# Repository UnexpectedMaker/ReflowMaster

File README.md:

# ReflowMaster

ReflowMaster is my original open source toaster oven reflow controller that I used to sell on tindie:
https://www.tindie.com/products/13378/

### This project is not compatible with ReflowMasterPro

It's custom hardware and custom code but all open source so if you want the challenge of making one yourself or you want to hack the code, go for it!

I have a live stream build of the board here if you want to see what's involved
https://www.youtube.com/watch?v=OGQ-GZZ90oE

# ReflowMaster Design Files

Included in this repository:
- EagleCAD schematics and Board layout files (Eagle 9.1) 
- Exported Gerber files (Gerber 274X)
- STL files for the 3D printed case
- Adrduino code

# Open Source License
The hardware design files are released as open source under the CERN license. Please review the license before using these files in your own projects to understand your obligations.

# STL files for 3D printing
I have included the STL files for the case and also the exhaust fan adapter I made for my specific toaster oven. 

**NOTE:** Do not print the exhaust fan in PLA, please use PET-G or ABS as PLA warps/melts at a low temp. Also DO NOT connect the 3D printed exhaust fan directly to the metal of teh oven, it will melt and ruin your oven. You will need to add some heat resistant insulator between the metal and the 3D print. 

# Which TFT?
The TFT I am using is a 2.4" SPI TFT using the ILI9341 Driver available via...

AliExpress
https://s.click.aliexpress.com/e/_DevvrLr

Ebay
https://rover.ebay.com/rover/1/705-53470-19255-0/1?icep_id=114&ipn=icep&toolid=20004&campid=5338252684&mpre=https%3A%2F%2Fwww.ebay.com.au%2Fitm%2F2-4-240x320-SPI-TFT-LCD-Serial-240-320-ILI9341-PCB-Adapter-SD-Card-M52%2F291549777432%3FssPageName%3DSTRK%253AMEBIDX%253AIT%26_trksid%3Dp2057872.m2749.l2649

# SAMD21 Bootloader
If you build your own Reflow Master, you will need to use a SAMD21G18 that already has an Arduino bootloader on it *before* it is put on the board. If you need to add a bootloader, you'll need an ATMEL ICE and an adapter for the chip. The cheapest adapter you can get is my SAMD21G Mangler available here...
https://www.tindie.com/products/13379/

# Updating firmware & Adding profiles - for Version 2.0.0
You can flash your Reflow Master with the Arduino IDE using the code provided above.

If you wish to add or change any of the reflow profiles, you need to do so in the code and re-flash the changes to your Reflow Master.

The Reflow Master board works like an "Adafruit Feather M0" - so you'll need to have the Adafruit Cortex m0 hardware profiles installed as well as the regular Cortex m0 Arduino profiles.

You can use the instructions here to install everything you need to get up and running in the Arduino IDE:
https://learn.adafruit.com/adafruit-feather-m0-basic-proto/setup

You will also need the following libraries from Library Manager
- One Button
- Adafruit_GFX
- Adafruit_ILI9341

Once you have everything you need, you can download the code from this repo and put it into the Arduino folder where your sketches are stored, load the sketch, select Adafruit Feather M0 from the boards list, plug in your RM and turn it on, and select the correct port from the ports list and flash.
   
The easiest way to put a new profile into the code is to change one of the existing profiles, by altering the values in it's class initialiser. Information of what each value is is available in the ReflowMasterProfile.h file:
https://github.com/UnexpectedMaker/ReflowMaster/blob/master/Code/Reflow_Master_v2/ReflowMasterProfile.h
   
Enjoy!

# Support Unexpected Maker

I love designing, making and releasing my projects as open source. I do it because I believe it’s important to share knowledge and give back to the community, like many have done before me. It helps us all learn and grow.

That said, a lot of time, effort and finances have gone into designing and releasing these files, so please consider supporting me by buying some of my products:

https://unexpectedmaker.com/shop

https://www.tindie.com/stores/seonr/

Or by becoming a Patron:

https://www.patreon.com/unexpectedmaker

# Join my discord server
https://discord.com/invite/xAHpApP

# Unexpected Maker
https://unexpectedmaker.com

http://youtube.com/unexpectedmaker

http://twitter.com/unexpectedmaker

https://www.facebook.com/unexpectedmaker/

https://www.instagram.com/unexpectedmaker/

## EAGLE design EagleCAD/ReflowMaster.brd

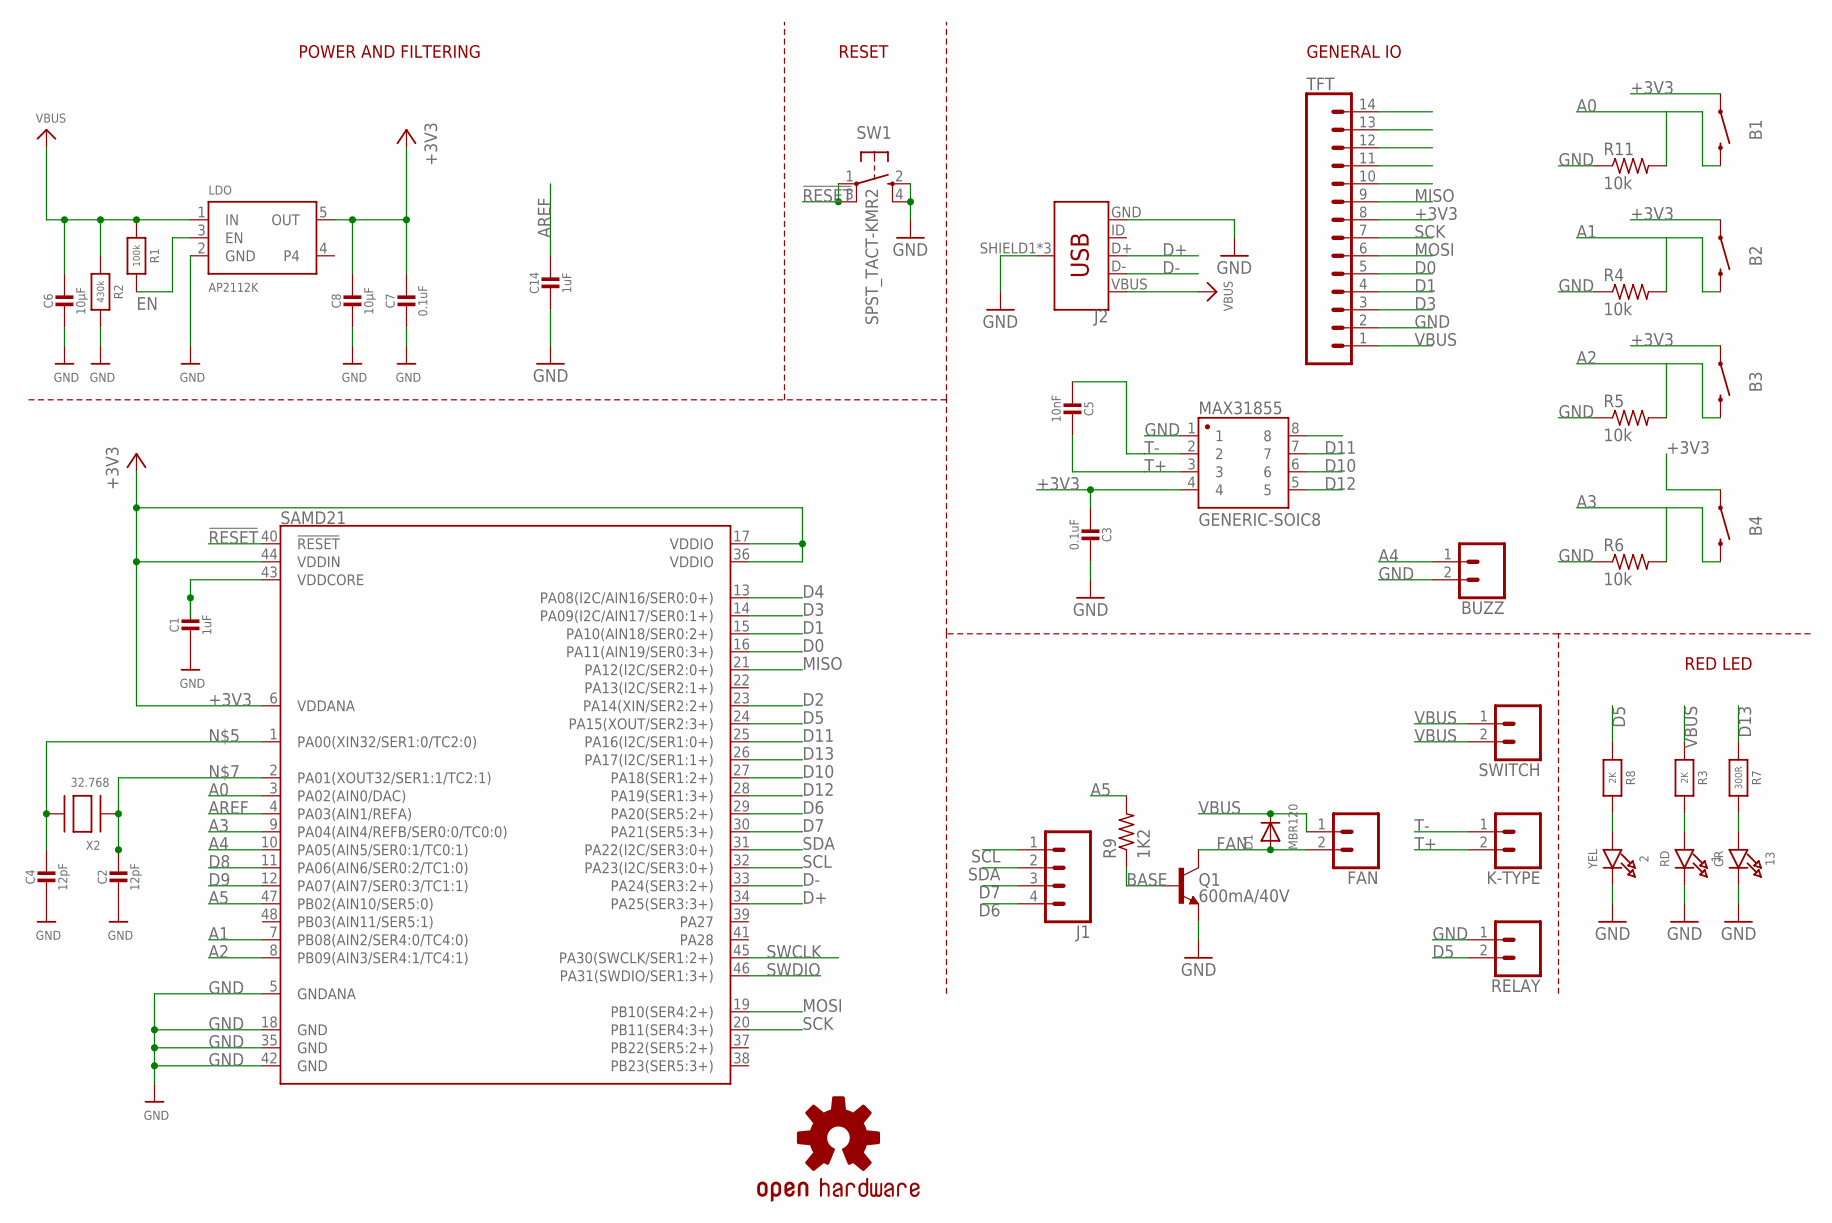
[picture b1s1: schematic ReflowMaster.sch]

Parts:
1: RD; CHIPLED_0805_NOOUTLINE
2: YEL; CHIPLED_0805_NOOUTLINE
13: GR; CHIPLED_0805_NOOUTLINE
B1, B2, B3, B4: MOMENTARY-SWITCH-SPST-PTH-RIGHT-ANGLE-KIT; TACTILE_SWITCH_PTH_RIGHT_ANGLE_KIT
BUZZ: CONN_02; 1X02
C1, C14: 1uF; 0805-NO
C2, C4: 12pF; 0805-NO
C3, C7: 0.1uF; 0805-NO
C5: 10nF; 0805-NO
C6, C8: 10µF; 0805-NO
D1: MBR120; SOD-123
FAN: CONN_02; 1X02
J1: CONN_041X04_NO_SILK; 1X04_NO_SILK
J2: USB_MICRO-B_FEMALE-SMT; USB-B-MICRO-SMD
K-TYPE: CONN_02; 1X02
LDO: AP2112K; SOT23-5
LOGO1: OSHW-LOGOS; OSHW-LOGO-S
MAX31855: GENERIC-SOIC8; SO08-UNIVERSAL
Q1: 600mA/40V; SOT23-3
R1: 100k; 0805-NO
R2: 430k; 0805-NO
R3, R8: 2K; 0805-NO
R4, R5, R6, R11: 10k; R0805
R7: 300R; 0805-NO
R9: 1K2; R0805
RELAY: CONN_02; 1X02
SAMD21: ATSAMD21G-A; TQFP-48
SW1: SPST_TACT-KMR2; KMR2
SWITCH: CONN_02; 1X02
TFT: CONN_14NO_SILK; 1X14_NO_SILK
X2: 32.768; XTAL3215

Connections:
!RESET: SAMD21.40 (!RESET!), SW1.1, SW1.3 (P1)
+3V3: B1.1, B2.1, B3.1, B4.1, C3.2, C7.1, C8.1, LDO.5 (OUT), MAX31855.4, SAMD21.6 (VDDANA), SAMD21.17 (VDDIO), SAMD21.36 (VDDIO), SAMD21.44 (VDDIN), TFT.8
A0: B1.2, R11.2, SAMD21.3 (PA02(AIN0/DAC))
A1: B2.2, R4.2, SAMD21.7 (PB08(AIN2/SER4:0/TC4:0))
A2: B3.2, R5.2, SAMD21.8 (PB09(AIN3/SER4:1/TC4:1))
A3: B4.2, R6.2, SAMD21.9 (PA04(AIN4/REFB/SER0:0/TC0:0))
A4: BUZZ.1, SAMD21.10 (PA05(AIN5/SER0:1/TC0:1))
A5: R9.2, SAMD21.47 (PB02(AIN10/SER5:0))
AREF: C14.1, SAMD21.4 (PA03(AIN1/REFA))
BASE: Q1.1 (B), R9.1
D0: SAMD21.16 (PA11(AIN19/SER0:3+)), TFT.5
D1: SAMD21.15 (PA10(AIN18/SER0:2+)), TFT.4
D2: SAMD21.23 (PA14(XIN/SER2:2+))
D3: SAMD21.14 (PA09(I2C/AIN17/SER0:1+)), TFT.3
D4: SAMD21.13 (PA08(I2C/AIN16/SER0:0+))
D5: R8.1, RELAY.2, SAMD21.24 (PA15(XOUT/SER2:3+))
D6: J1.4, SAMD21.29 (PA20(SER5:2+))
D7: J1.3, SAMD21.30 (PA21(SER5:3+))
D8: SAMD21.11 (PA06(AIN6/SER0:2/TC1:0))
D9: SAMD21.12 (PA07(AIN7/SER0:3/TC1:1))
D10: MAX31855.6, SAMD21.27 (PA18(SER1:2+))
D11: MAX31855.7, SAMD21.25 (PA16(I2C/SER1:0+))
D12: MAX31855.5, SAMD21.28 (PA19(SER1:3+))
D13: R7.1, SAMD21.26 (PA17(I2C/SER1:1+))
D+: J2.D+, SAMD21.34 (PA25(SER3:3+))
D-: J2.D-, SAMD21.33 (PA24(SER3:2+))
EN: LDO.3 (EN), R1.2
FAN: D1.A, FAN.2, Q1.3 (C)
GND: 1.C, 2.C, 13.C, BUZZ.2, C1.2, C2.2, C3.1, C4.2, C6.2, C7.2, C8.2, C14.2, J2.GND, J2.SHIELD1 (SHIELD), J2.SHIELD2 (SHIELD), J2.SHIELD3 (SHIELD), LDO.2 (GND), MAX31855.1, Q1.2 (E), R2.2, R4.1, R5.1, R6.1, R11.1, RELAY.1, SAMD21.5 (GNDANA), SAMD21.18 (GND), SAMD21.35 (GND), SAMD21.42 (GND), SW1.2 (S), SW1.4 (S1), TFT.2
MISO: SAMD21.21 (PA12(I2C/SER2:0+)), TFT.9
MOSI: SAMD21.19 (PB10(SER4:2+)), TFT.6
unnamed: 1.A, R3.2
unnamed: 13.A, R7.2
unnamed: 2.A, R8.2
unnamed: C4.1, SAMD21.1 (PA00(XIN32/SER1:0/TC2:0)), X2.P$2
unnamed: C2.1, SAMD21.2 (PA01(XOUT32/SER1:1/TC2:1)), X2.P$1
SCK: SAMD21.20 (PB11(SER4:3+)), TFT.7
SCL: J1.1, SAMD21.32 (PA23(I2C/SER3:0+))
SDA: J1.2, SAMD21.31 (PA22(I2C/SER3:0+))
SWCLK: SAMD21.45 (PA30(SWCLK/SER1:2+))
SWDIO: SAMD21.46 (PA31(SWDIO/SER1:3+))
T+: C5.1, K-TYPE.2, MAX31855.3
T-: C5.2, K-TYPE.1, MAX31855.2
VBUS: C6.1, D1.C, FAN.1, J2.VBUS, LDO.1 (IN), R1.1, R2.1, R3.1, SWITCH.1, SWITCH.2, TFT.1
VDDCORE: C1.1, SAMD21.43 (VDDCORE)

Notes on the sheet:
POWER AND FILTERING
RESET
GENERAL IO
RED LED

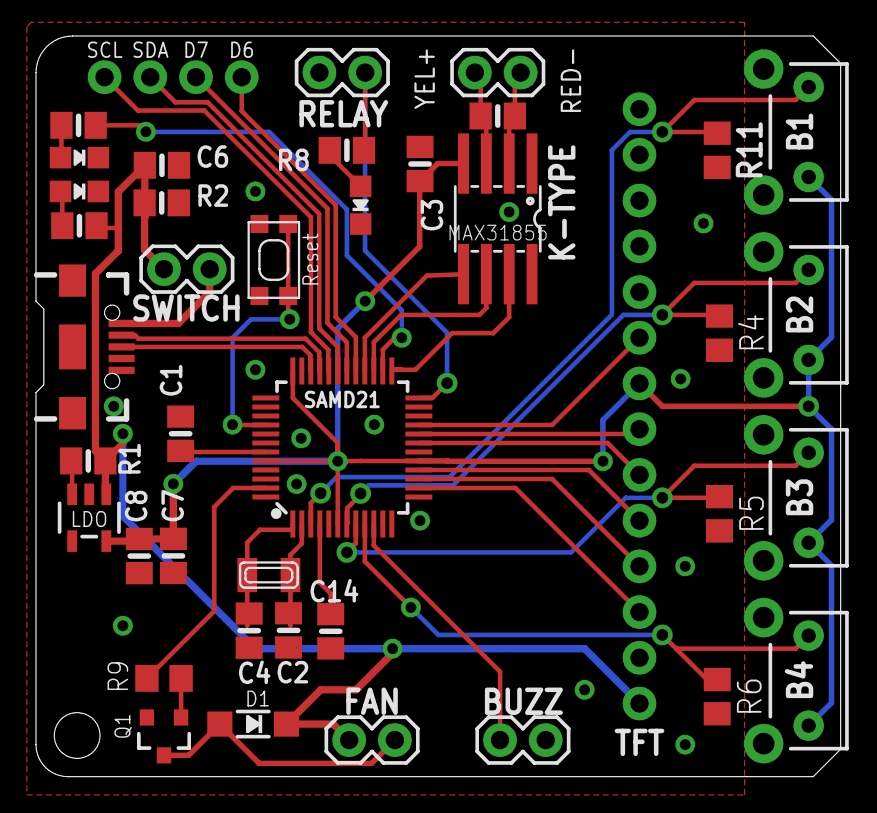
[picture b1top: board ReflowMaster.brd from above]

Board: 2 copper layers, 44.7 x 41.1 mm, 42 parts (1 on the bottom side), 39 nets.

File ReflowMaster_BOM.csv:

Qty,Value,Device,Package,Parts,Description,PROD_ID,SF_SKU,VALUE,
1,,ATSAMD21G-A,TQFP-48,SAMD21,Atmel SAMD21G SMART ARM-Based Microcontroller,IC-13064,,,
5,,HEADER,1X02,"BUZZ, FAN, K-TYPE, RELAY, SWITCH",0.1” Header,,,,
1,,HEADER,1X04_NO_SILK,J1,0.1” Header,CONN-09696,,,
1,,HEADER,1X14_NO_SILK,TFT,0.1” Header,,,,
1,,USB-B-MICRO-SMD,USB-B-MICRO-SMD,J2,USB Type Micro-B Connector,CONN-11752,,,
2,0.1uF,CAPACITOR,0805,"C3, C7",Ceramic Capacitors,,,,
1,100k,RESISTOR,0805,R1,RESISTOR,,,,
4,10k,RESISTOR,0805,"R4, R5, R6, R11",RESISTOR,,,,
1,10nF,CAPACITOR,0805,C5,Ceramic Capacitors,,,,
2,10uF,CAPACITOR,0805,"C6, C8",Ceramic Capacitors,,,,
2,12pF,CAPACITOR,0805,"C2, C4",Ceramic Capacitors,,,,
1,1K2,RESISTOR,0805,R9,RESISTOR,,,,
2,1uF,CAPACITOR,0805,"C1, C14",Ceramic Capacitors,,,,
2,2K,RESISTOR,0805,"R3, R8",RESISTOR,,,,
1,300R,RESISTOR,0805,R7,RESISTOR,,,,
1,32.768,XTAL-3.2X1.5,XTAL3215,X2,SMT Crsytal,,,,
1,430k,RESISTOR,0805,R2,RESISTOR,,,,
1,600mA/40V,TRANS_NPN-MMBT2222AL,SOT23-3,Q1,NPN transistor,TRANS-08049,,600mA/40V,
1,AP2112K,VREG_SOT23-5,SOT23-5,LDO,SOT23-5 Fixed Voltage Regulators,,,,
1,GENERIC-SOIC8,GENERIC-SOIC8,SO08-UNIVERSAL,MAX31855,Generic narrow & wide SOIC8,,,,
1,GR,LED,0805,13,LED,,,,
1,MBR120,DIODESOD-123,SOD-123,D1,Diode,,,,
4,SWITCH-SPST,SWITCH-SPST,TACTILE_SWITCH_PTH_RIGHT_ANGLE_KIT,"B1, B2, B3, B4",Momentary Switch (Pushbutton) - SPST,CONN-10672,COM-10791,,
1,RD,LED,0805,1,LED,,,,
1,SPST_TACT-KMR2,SPST_TACT-KMR2,KMR2,SW1,"SMT 6mm switch, EVQQ2 series",,,,
1,YEL,LED,0805,2,LED,,,,

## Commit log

2018-08-10 Added STL files for the 3D printed case
2018-08-11 Added PDF of the schematic and BOM parts list
2018-08-12 Upped code to v1.01 Settings UI button now change to show SELECT or CHANGE depending on what is selected
2018-08-27 Added tangents to the curve for ESP32 support Improved graph curves Fixed some UI glitches Made end graph time value be the end profile time
2018-08-27 esp32 support, mosty commenting stuff out
    ### todo
    removes flashstorage to be abstracted into methods and add ifdef wraps
    esp32 flash storage support for read and write methods
    esp32 tone buzzer
    esp32 relay pwm use sigmandelta or ledc abstract to start and wriite methods
2018-08-27 restored samd pins
2018-08-28 Moved to averaged temp reading to help reduce probe noise Temp is now read 10 times per second and averaged.
2018-08-31 Added new 8.5mm header variant and updated 5mm variant for the front of the Reflow Master cases Added info about the files
2019-02-08 Added STL for exhaust fan
2019-02-08 Added notes in readme for the STL file for the air exhaust fan
2019-05-28 Updated BOM + Schematic pDF + Eagle files with missing part types Changed 12.5pF caps for XTAL to 12pF caps.
2019-07-07 07/09/2019 v1.05 - Fixed some bugs, Thanks Tablatronix!
    20/05/2019 v1.04
    - Increased max curve array size to support profiles up to 8mins
    - Added fan on time after reflow for cooldown settings to keep the fan on for X seconds to help cool the oven down
    - Added extra profile for Ju Feng Medium temp paste - 183deg - No Clean 63CR218 Sn64/Bi35/AG1
2019-07-26 Updated the STL for the front of the case
2019-08-06 Added missing license files and readme
2019-09-16 Fixed probe temp offset not being changeable in settings Added version history to readme
2019-09-16 Fixed bad formatting in readme
2020-07-01 Updated all of the STL files for the different case versions
2020-07-02 Updated to latest Reflow Master Arduino code
    02/07/2020 v1.07
    - Cleaned up some Fan control and tracking code
    - Cleaned up some debug messages
2020-07-13 Fixed bug in DEBUG mode
2020-09-06 Add profile for CHIPQUICK TS391AX
2020-09-28 Build with platformio.
2020-09-28 Code formatting. Whitespace changes only.
2020-09-28 Vendor libraries that aren't easily available.
2020-09-28 Ok, MAX31855 is a available PIO library, just use that. Also, add .gitignore.
2020-09-28 Fix all build warnings. Mostly lots of unsigned/signed comparisons, and removed `char* string2char(String command)` because it was an abomination.
2020-09-28 Use sane types for things. Mostly, use enums for state, instead of magic numbers everywhere. Also, add facilities for managing inverted-output fan/SSR signals.
2020-12-19 Added version 2.0.0 project code with new bake feature!
2020-12-19 Updated to v2.01 New - Increased max bake time to 3 hours - Added long press for Bake Time & Temp to quickly change values, clamped at max, so it won't loop Fixes - Forgot to hookup minBakeTemp, minB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
2020-12-20 Version 2.02 - Prevent going into the bake menu when there is a TC error - Set FAN to Off by default in settings - Fixed some incorrect comments - Made TC error more visible on menu screen
2020-12-21 Fixed UI glitch in main menu with TC error display Keeping version at 2.02
2021-01-31 Update README.md
    Added discord server link
2021-03-01 Added Chipquick TS391AX paste profile
    01/03/2021 v2.03 - Added Chipquick TS391AX paste profile
    - Adjusted SETTINGS_PASTE to fit 6 profiles in to screen
    - Adjusted cursor movement on SETTINGS_PASTE screen
2021-03-01 Add .vscode to .gitignore
2021-03-01 Add profile for CHIPQUICK TS391AX paste
    01/03/2021 v1.09 - Add profile for CHIPQUICK TS391AX paste
    - Adjusted SETTINGS_PASTE (state == 12) to fit 6 profiles in to screen
    - Adjusted cursor movement on SETTINGS_PASTE (state == 12) screen
2021-05-20 Make millis() tracking variables unsigned
2021-05-20 Remove unused variables
2021-05-20 Fix signed vs unsigned comparison errors
    size_t for element comparison, and signed int for the settings_pointer (so decrementing can check for -1 without rollover)
2021-05-20 Remove string2char helper
    Unless I'm missing something I believe this is ill-formed? The String is passed by copy and this returns a pointer to the underlying heap memory, so it's possible that the memory will get overwritten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
    Instead we can just pass the c_str() directly, as the function doesn't care about const-ness. This eliminates the compiler warning that function may fail to return a pointer if the string is 0 length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
2021-05-20 Update gitignore for Visual Studio / Visual Micro
2021-05-20 Refactor ShowMenuOptions as ShowButtonOptions
    Distinguishing between the current menu items and the buttons to control them
2021-05-20 Create linked list settings menu
2021-05-21 Add scrolling feature to settings menu
    Now supports an "infinite" (2^16) number of menu items!
2021-05-21 Add scroll position indicator to settings menu
2021-05-22 Fix indexing error for settings menu pagination
    9 items per page, not 8. Caused by indexing 'items per' at 1 and the items themselves at 0.
2021-05-22 Create paged scroll mode for menu settings
    Not quite as pretty as filling the whole screen with options no matter where you are, but more efficient to redraw it once rather than every time the user pushes down.
2021-05-26 Move scroll and page indicators to main file
    Because these work around the buttons and are not specific to the settings page, I'm moving them to the main file so they can (potentially) be called by other menu modes.
2021-05-26 Replace SetDefaults with copy constructor
    All defaults are set in the struct definition itself. This avoids mixed messages about what settings are actually 'default'.
2021-05-26 Reword buzzer disable settings option
2021-05-26 Fix minor settings menu redraw issues
    Don't do a 'clear all' on the buttons to avoid clipping long menu items at the end of the list, and clear the description box on redraw for description text longer than the 'standard' items area.
2021-05-26 Add key tone option to settings menu
    To disable the buzzer, but ONLY when pressing buttons and not for functional purposes (e.g. opening the oven door at the end of reflow).
2021-05-26 Add menu option to disable the buzzer
    STOP. FREAKING. BEEPING.
2021-05-26 Change struct values to match SetDefaults()
2021-05-26 Set button colors automatically
    Avoids having to repeat the colors everywhere, and makes it easier to change them. Can still be overridden if necessary.
2021-05-26 Create DrawButton helper function
2021-05-26 Flash buttons when failing to enter mode
    Visual feedback that the mode can't be entered. Particularly useful when the buzzer is disabled.
2021-05-26 Loop settings menu pointer
    Allows the pointer to loop around from the bottom to the top and vice-versa. Helpful for long settings lists.
2021-05-26 Do not reset pointer on setting default cancel
    Small quality of life change, but if you cancel the "reset to default" menu option, the menu stays at that setting (and that page) instead of starting over at 0.
2021-05-26 Refactor linked list 'geIIndex' to use 'ItemAt'
    Making it clear that we're returning the object rather than some reference to position
2021-05-26 Redraw menu value separately from name
    Reduces flickering by only updating the menu item value rather than the name and value (at the expense of calculating the text bounds each call)
2021-05-26 Move button text string option to class
2021-05-26 Move settings pointer update out of buttons
    Otherwise this is called twice
2021-05-26 Refactor UpdateSettingsPointer as 'Draw'
    Since this function isn't "updating" anything but the display, and the name makes me think it's doing calculations on the pointer value itself.
2021-05-27 Remove 'refresh on change' setting parameter
    This is redundant, as all modes with "SELECT" are used to load new pages and do not need to refresh on change.
2021-06-12 Move TFT include and colors to dedicated header
2021-06-12 Refactor indicator functions from 'Show' to 'Draw'
2021-06-12 Move settings button functionality to class
    Allowing the class to override these buttons as-needed.
2021-06-12 Create dedicated selection var for settings class
    Not strictly necessary, but increases encapsulation and avoids any weirdness with modifying the global selection value when switching between menus.
2021-06-12 Move related settings 'draw' functions to member
    This way the entire page is drawn with a call to 'draw' (something something encapsulation).
2021-06-12 Privatize addl. exposed settings menu functions
2021-06-13 Create ClearButton function
    For overwriting the button text exactly, rather than bulk clearing an area.
2021-08-21 Change menu page from class to namespace
    These functions were all static anyways, and this better fits with the mostly functional programming at use elsewhere.
2021-08-21 Move SettingsOption variables to private
    Better encapsulation yada yada
2021-10-21 Use polymorphism for setting option types
2021-10-21 Add startup tune option (on by default)
2021-10-25 Remove redundant functions for option links
    Handling nullptr for the 'get' function, and going directly to the 'show' pages rather than using a helper.
2021-10-31 Put tc.getInternal() back in after previous merge.
    Calling tc.getInternal() is required by the Max chip to do proper cold junction compensation at the time of reading the actual TC temperature.
2021-10-31 Fix compilation error and warning from 423e6ef
    The previous commit is missing a semicolon on line 812 which breaks compilation.
    While the getInternal() function call is apparently needed this removes the variable allocations which are not (and are generating a warning).
2022-02-16 Push latest 2.04 version
2022-07-06 Fixed spline error using latest board manager version for Adafruit SAMD boards (>1.6.6) Updated version to 2.0.5
2024-01-13 Update README.md
    Fixed broken link to TFT display on ALIExpress
2024-07-03 Added note about incompatibility with RMP

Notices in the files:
EagleCAD/ReflowMaster.sch:
COPYRIGHT: 2018
parts and their libraries:
microbuilder: This work is placed in the public domain, and may be freely used for commercial and non-commercial work with the following conditions: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
SparkFun-IC-Microcontroller: Licensing: Creative Commons ShareAlike 4.0 International - https://creativecommons.org/licenses/by-sa/4.0
